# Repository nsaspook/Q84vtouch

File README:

Turbopump RS485 DCU readout emulator

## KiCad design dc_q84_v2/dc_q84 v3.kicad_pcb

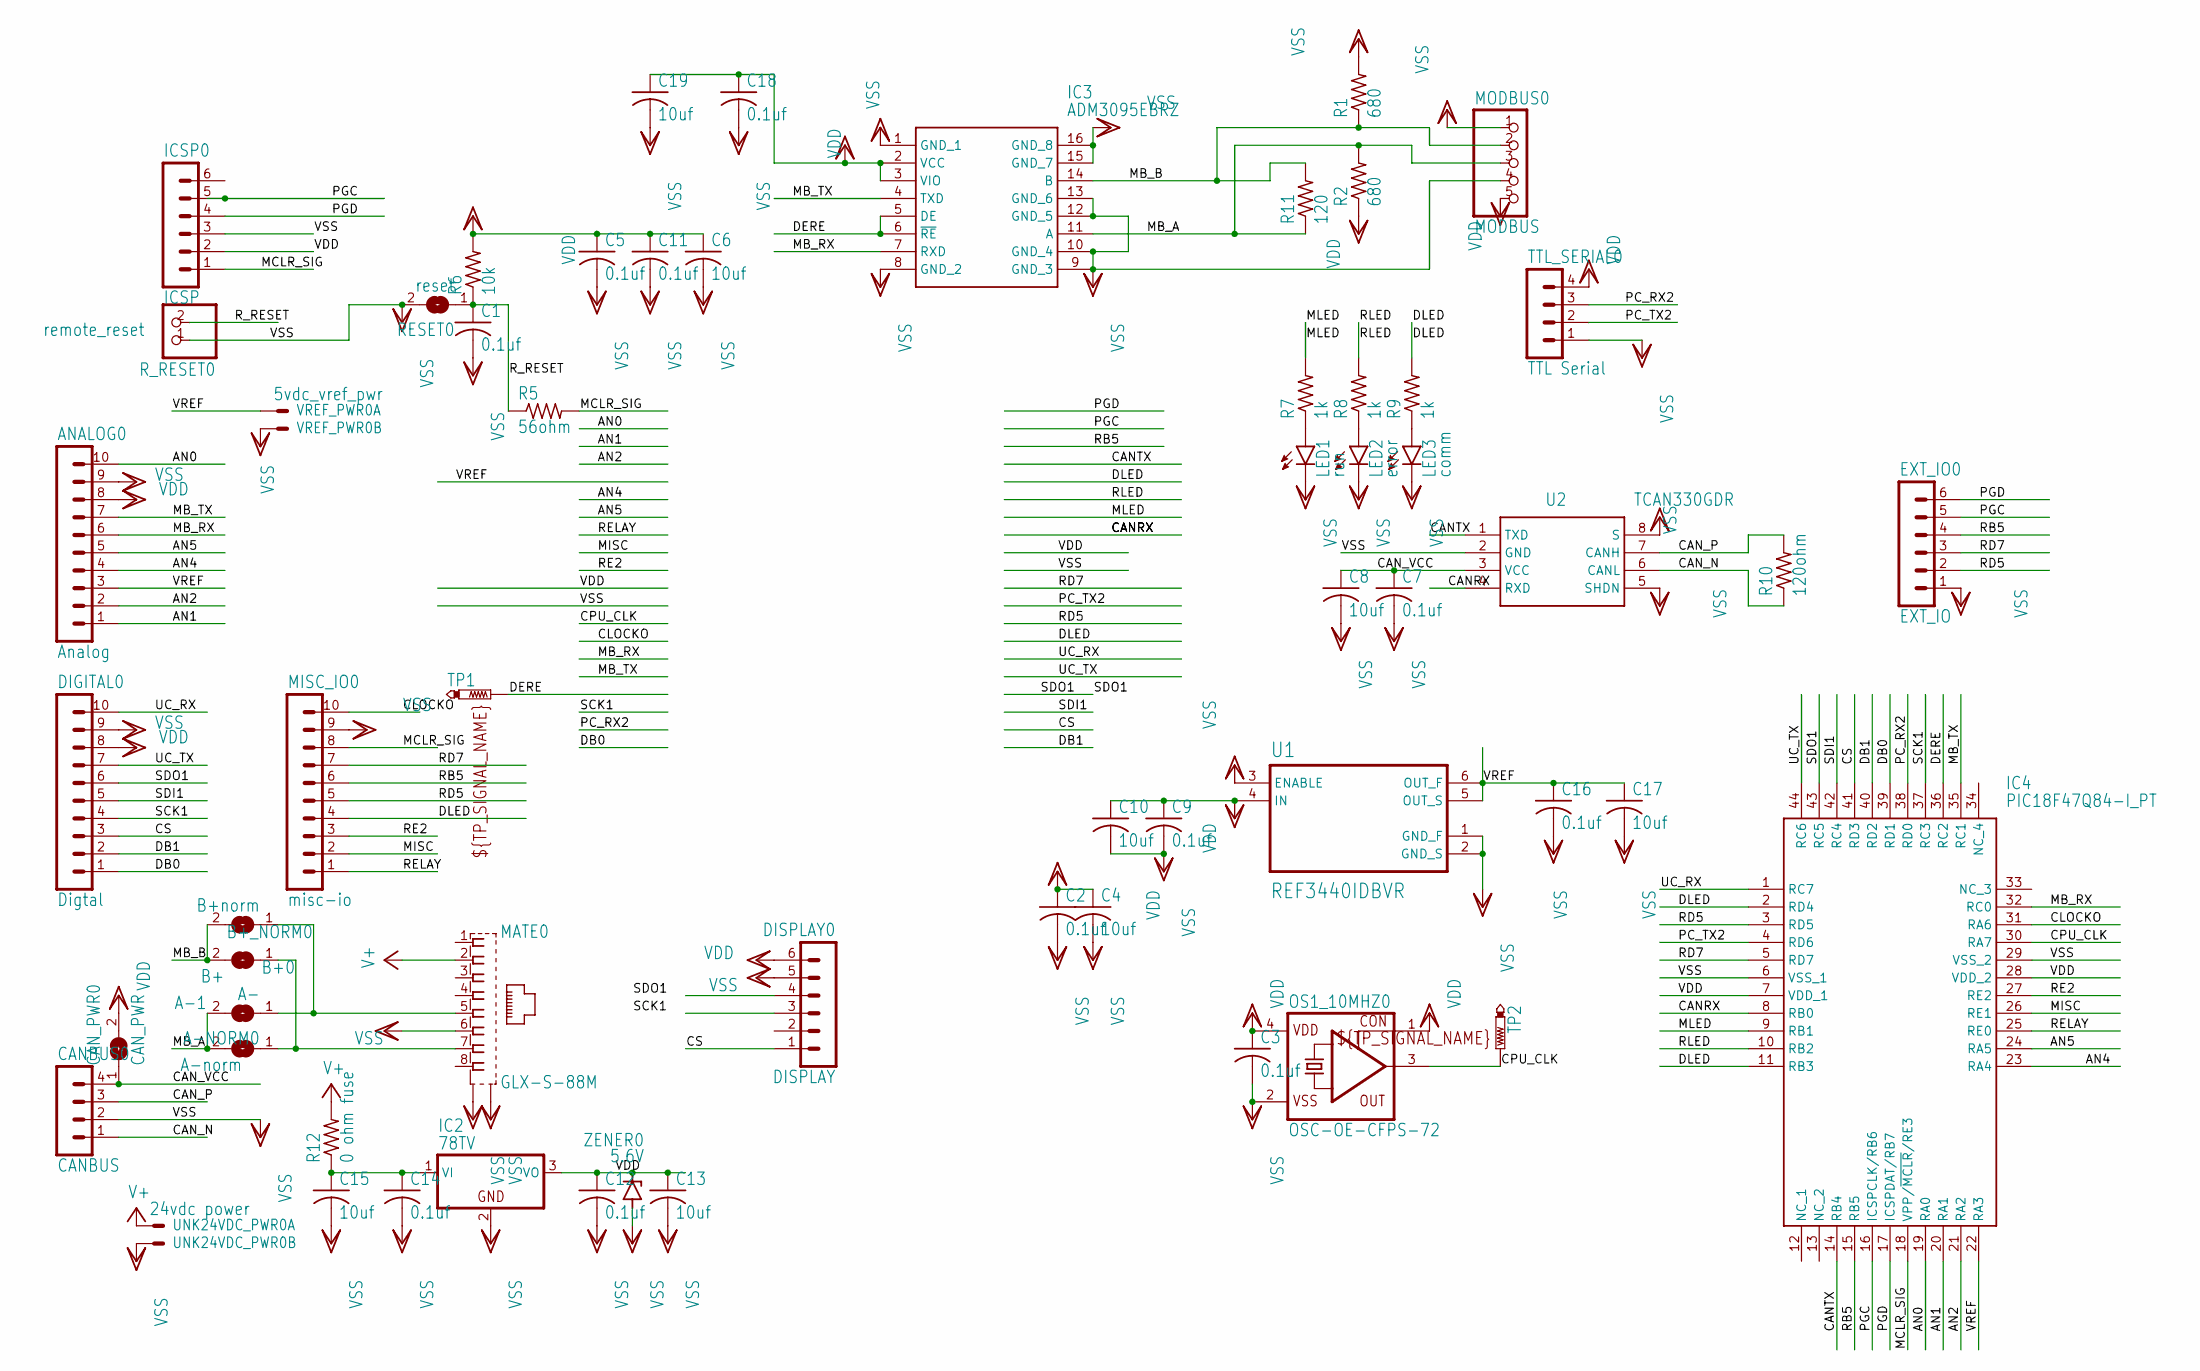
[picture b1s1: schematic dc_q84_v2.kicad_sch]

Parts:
A-1: A-; SJ
A-NORM0: A-norm; SJ
ANALOG0: Analog; MA10-1
B+0: B+; SJ
B+_NORM0: B+norm; SJ
C1, C2, C3, C5, C7, C9, C11, C12, C14, C16, C18: 0.1uf; C0805
C4, C6, C8, C10, C13, C15, C17, C19: 10uf; C0805
CANBUS0: CANBUS; MA04-1
CAN_PWR0: CAN_PWR; SJ
DIGITAL0: Digtal; MA10-1
DISPLAY0: DISPLAY; MA06-1
EXT_IO0: EXT_IO; MA06-1
IC2: 78TV; TO220V
IC3: ADM3095EBRZ; SOIC127P600X175-16N
IC4: PIC18F47Q84-I_PT; QFP80P1200X1200X120-44N
ICSP0: ICSP; MA06-1
LED1: run; CHIPLED_0805
LED2: error; CHIPLED_0805
LED3: comm; CHIPLED_0805
MATE0: GLX-S-88M
MISC_IO0: misc-io; MA10-1
MODBUS0: MODBUS; 1X05
OS1_10MHZ0: OSC-OE-CFPS-72; 7.2X5.2-4-PAD
R1, R2: 680; R0805
R5: 56ohm; R0805
R6: 10k; R0805
R7, R8, R9: 1k; R0805
R10: 120ohm; R0805
R11: 120; R0805
R12: 0 ohm fuse; R1206
RESET0: reset; SJ
R_RESET0: remote_reset; 1X02
TP1, TP2: PTR1PAD1-13; P1-13
TTL_SERIAL0: TTL Serial; MA04-1
U1: REF3440IDBVR; SOT95P280X145-6N
U2: TCAN330GDR; SOIC127P600X175-8N
UNK24VDC_PWR0: 24vdc power; 22-23-2021
VREF_PWR0: 5vdc_vref_pwr; 22-23-2021
ZENER0: 5.6V; SMB

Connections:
AN0: ANALOG0.10, IC4.19 (RA0)
AN1: ANALOG0.1, IC4.20 (RA1)
AN2: ANALOG0.2, IC4.21 (RA2)
AN4: ANALOG0.4, IC4.23 (RA4)
AN5: ANALOG0.5, IC4.24 (RA5)
CANRX: IC4.8 (RB0), U2.4 (RXD)
CANTX: IC4.14 (RB4), U2.1 (TXD)
CAN_N: CANBUS0.1, R10.1, U2.6 (CANL)
CAN_P: CANBUS0.3, R10.2, U2.7 (CANH)
CAN_VCC: C7.1, C8.1, CANBUS0.4, CAN_PWR0.1, U2.3 (VCC)
CLOCKO: IC4.31 (RA6), MISC_IO0.10
CPU_CLK: IC4.30 (RA7), OS1_10MHZ0.3 (OUT), TP2.TP
CS: DIGITAL0.3, DISPLAY0.1, IC4.41 (RD3)
DB0: DIGITAL0.1, IC4.39 (RD1)
DB1: DIGITAL0.2, IC4.40 (RD2)
DERE: IC3.5 (DE), IC3.6 (~RE), IC4.36 (RC2), TP1.TP
DLED: IC4.2 (RD4), IC4.11 (RB3), MISC_IO0.4, R9.2
MB_A: A-1.2, A-NORM0.2, IC3.11 (A), MODBUS0.3, R2.2, R11.1
MB_B: B+0.2, B+_NORM0.2, IC3.14 (B), MODBUS0.2, R1.1, R11.2
MB_RX: ANALOG0.6, IC3.7 (RXD), IC4.32 (RC0)
MB_TX: ANALOG0.7, IC3.4 (TXD), IC4.35 (RC1)
MCLR_SIG: IC4.18 (VPP/~MCLR/RE3), ICSP0.1, MISC_IO0.8, R5.2
MISC: IC4.26 (RE1), MISC_IO0.2
MLED: IC4.9 (RB1), R7.2
unnamed: A-NORM0.1, B+0.1, MATE0.7
unnamed: C14.1, C15.1, IC2.1 (VI), R12.1
unnamed: A-1.1, B+_NORM0.1, MATE0.5
unnamed: LED1.A, R7.1
unnamed: LED2.A, R8.1
unnamed: LED3.A, R9.1
PC_RX2: IC4.38 (RD0), TTL_SERIAL0.3
PC_TX2: IC4.4 (RD6), TTL_SERIAL0.2
PGC: EXT_IO0.5, IC4.16 (ICSPCLK/RB6), ICSP0.5
PGD: EXT_IO0.6, IC4.17 (ICSPDAT/RB7), ICSP0.4
RB5: EXT_IO0.4, IC4.15 (RB5), MISC_IO0.6
RD5: EXT_IO0.2, IC4.3 (RD5), MISC_IO0.5
RD7: EXT_IO0.3, IC4.5 (RD7), MISC_IO0.7
RE2: IC4.27 (RE2), MISC_IO0.3
RELAY: IC4.25 (RE0), MISC_IO0.1
RLED: IC4.10 (RB2), R8.2
R_RESET: C1.1, R5.1, R6.1, RESET0.1, R_RESET0.2
SCK1: DIGITAL0.4, DISPLAY0.3, IC4.37 (RC3)
SDI1: DIGITAL0.5, IC4.42 (RC4)
SDO1: DIGITAL0.6, DISPLAY0.4, IC4.43 (RC5)
UC_RX: DIGITAL0.10, IC4.1 (RC7)
UC_TX: DIGITAL0.7, IC4.44 (RC6)
V+: MATE0.2, R12.2, UNK24VDC_PWR0.1
VDD: ANALOG0.8, C2.1, C3.1, C4.1, C5.1, C6.1, C9.1, C10.1, C11.1, C12.1, C13.1, C18.1, C19.1, CAN_PWR0.2, DIGITAL0.8, DISPLAY0.6, IC2.3 (VO), IC3.2 (VCC), IC3.3 (VIO), IC4.7 (VDD_1), IC4.28 (VDD_2), ICSP0.2, MODBUS0.5, OS1_10MHZ0.1 (CON), OS1_10MHZ0.4 (VDD), R2.1, R6.2, TTL_SERIAL0.4, U1.4 (IN), ZENER0.C
VREF: ANALOG0.3, C16.1, C17.1, IC4.22 (RA3), U1.5 (OUT_S), U1.6 (OUT_F), VREF_PWR0.1
VSS: ANALOG0.9, C1.2, C2.2, C3.2, C4.2, C5.2, C6.2, C7.2, C8.2, C9.2, C10.2, C11.2, C12.2, C13.2, C14.2, C15.2, C16.2, C17.2, C18.2, C19.2, CANBUS0.2, DIGITAL0.9, DISPLAY0.5, EXT_IO0.1, IC2.2 (GND), IC3.1 (GND_1), IC3.8 (GND_2), IC3.9 (GND_3), IC3.10 (GND_4), IC3.12 (GND_5), IC3.13 (GND_6), IC3.15 (GND_7), IC3.16 (GND_8), IC4.6 (VSS_1), IC4.29 (VSS_2), ICSP0.3, LED1.C, LED2.C, LED3.C, MATE0.6, MATE0.S1, MATE0.S2, MISC_IO0.9, MODBUS0.1, MODBUS0.4, OS1_10MHZ0.2 (VSS), R1.2, RESET0.2, R_RESET0.1, TTL_SERIAL0.1, U1.1 (GND_F), U1.2 (GND_S), U1.3 (ENABLE), U2.2 (GND), U2.5 (SHDN), U2.8 (S), UNK24VDC_PWR0.2, VREF_PWR0.2, ZENER0.A

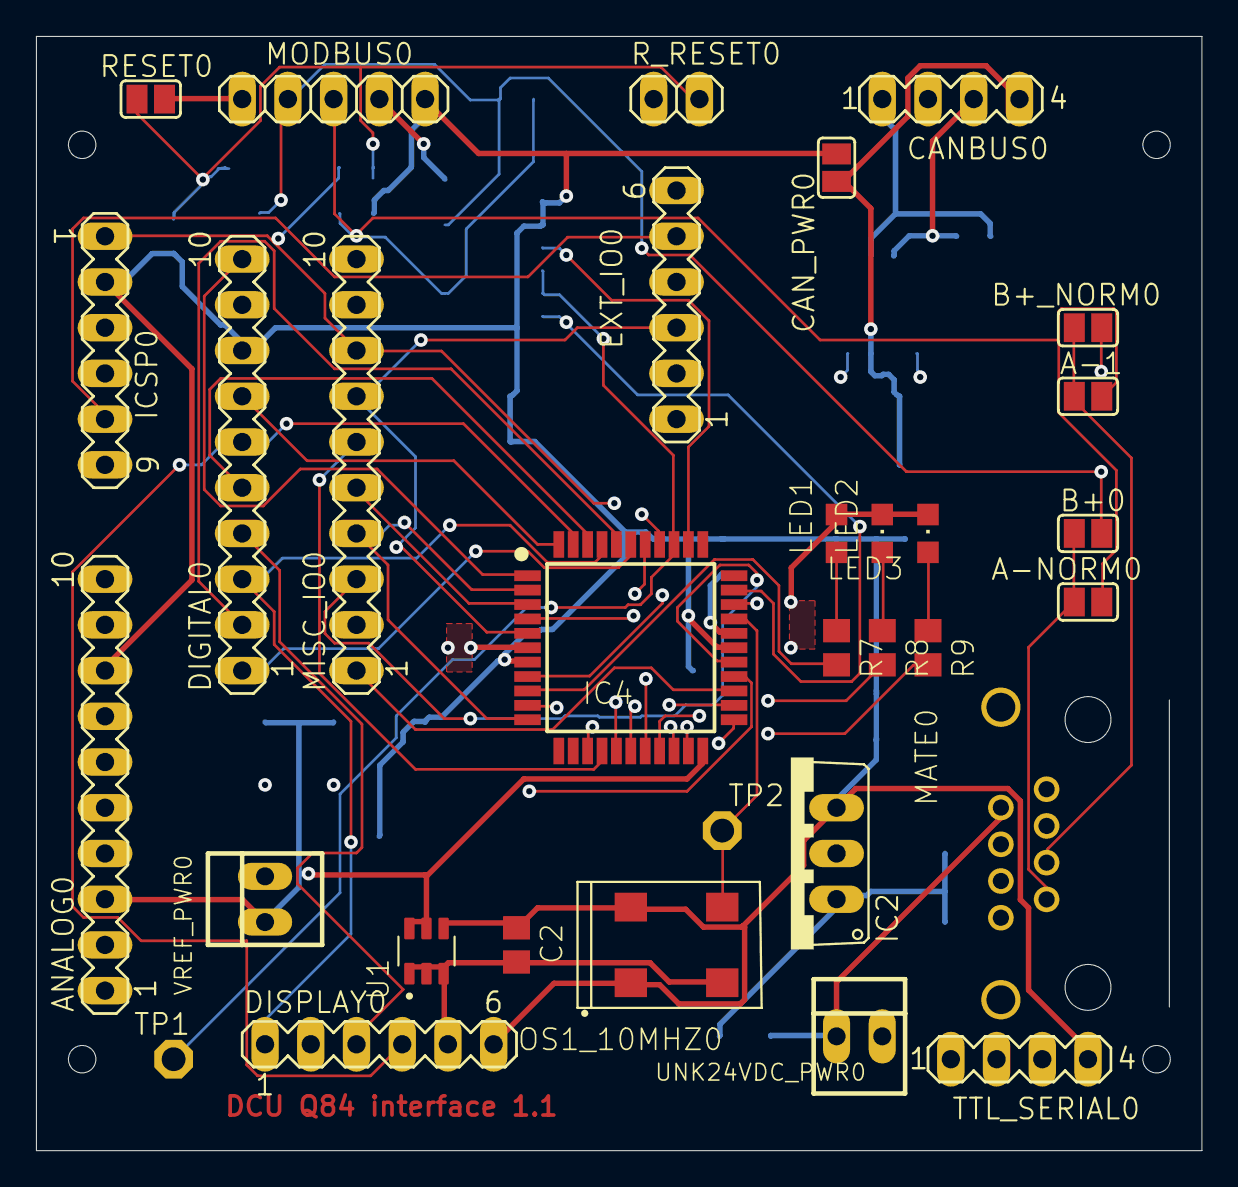
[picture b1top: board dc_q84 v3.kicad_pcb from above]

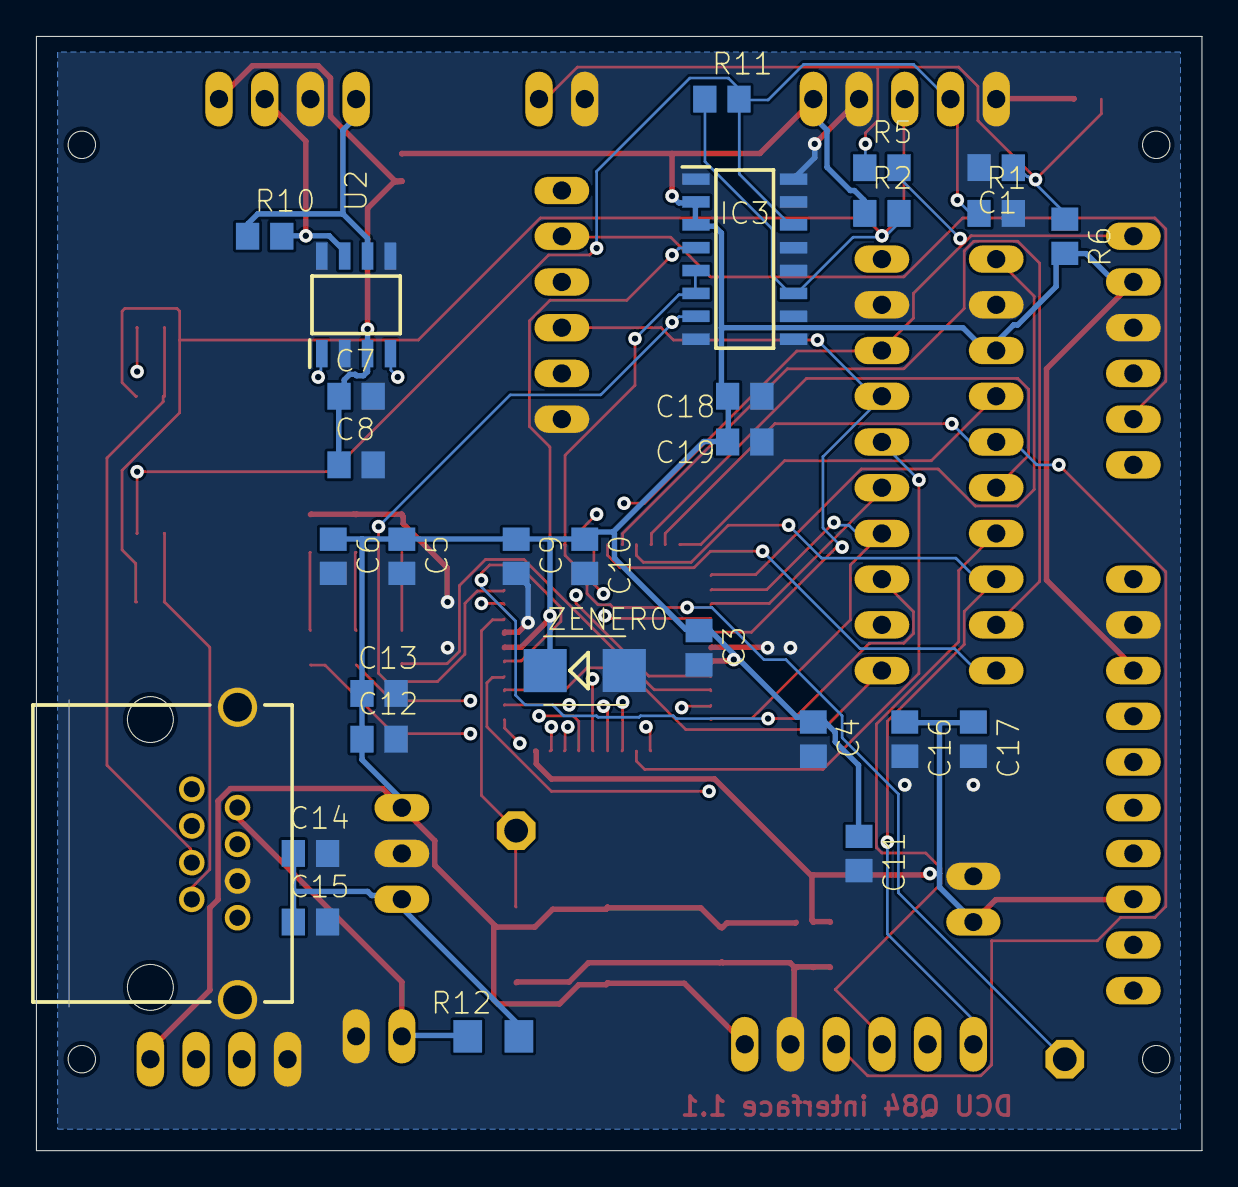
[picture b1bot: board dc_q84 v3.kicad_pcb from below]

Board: 4 copper layers, 64.8 x 61.9 mm, 64 parts (28 on the bottom side), 50 nets.

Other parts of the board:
@HOLE0, @HOLE1, @HOLE2, @HOLE3: (no value)

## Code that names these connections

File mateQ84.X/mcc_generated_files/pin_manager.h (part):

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// get/set channel_ANA0 aliases
#define channel_ANA0_TRIS                 TRISAbits.TRISA0
#define channel_ANA0_LAT                  LATAbits.LATA0
#define channel_ANA0_PORT                 PORTAbits.RA0
#define channel_ANA0_WPU                  WPUAbits.WPUA0
#define channel_ANA0_OD                   ODCONAbits.ODCA0
#define channel_ANA0_ANS                  ANSELAbits.ANSELA0
#define channel_ANA0_SetHigh()            do { LATAbits.LATA0 = 1; } while(0)
#define channel_ANA0_SetLow()             do { LATAbits.LATA0 = 0; } while(0)
#define channel_ANA0_Toggle()             do { LATAbits.LATA0 = ~LATAbits.LATA0; } while(0)
#define channel_ANA0_GetValue()           PORTAbits.RA0
#define channel_ANA0_SetDigitalInput()    do { TRISAbits.TRISA0 = 1; } while(0)
#define channel_ANA0_SetDigitalOutput()   do { TRISAbits.TRISA0 = 0; } while(0)
#define channel_ANA0_SetPullup()          do { WPUAbits.WPUA0 = 1; } while(0)
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// get/set M_SWITCH aliases
#define M_SWITCH_TRIS                 TRISAbits.TRISA1
#define M_SWITCH_LAT                  LATAbits.LATA1
#define M_SWITCH_PORT                 PORTAbits.RA1
#define M_SWITCH_WPU                  WPUAbits.WPUA1
#define M_SWITCH_OD                   ODCONAbits.ODCA1
#define M_SWITCH_ANS                  ANSELAbits.ANSELA1
#define M_SWITCH_SetHigh()            do { LATAbits.LATA1 = 1; } while(0)
#define M_SWITCH_SetLow()             do { LATAbits.LATA1 = 0; } while(0)
#define M_SWITCH_Toggle()             do { LATAbits.LATA1 = ~LATAbits.LATA1; } while(0)
#define M_SWITCH_GetValue()           PORTAbits.RA1
#define M_SWITCH_SetDigitalInput()    do { TRISAbits.TRISA1 = 1; } while(0)
#define M_SWITCH_SetDigitalOutput()   do { TRISAbits.TRISA1 = 0; } while(0)
#define M_SWITCH_SetPullup()          do { WPUAbits.WPUA1 = 1; } while(0)
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// get/set L_SWITCH aliases
#define L_SWITCH_TRIS                 TRISAbits.TRISA2
#define L_SWITCH_LAT                  LATAbits.LATA2
#define L_SWITCH_PORT                 PORTAbits.RA2
#define L_SWITCH_WPU                  WPUAbits.WPUA2
#define L_SWITCH_OD                   ODCONAbits.ODCA2
#define L_SWITCH_ANS                  ANSELAbits.ANSELA2
#define L_SWITCH_SetHigh()            do { LATAbits.LATA2 = 1; } while(0)
#define L_SWITCH_SetLow()             do { LATAbits.LATA2 = 0; } while(0)
#define L_SWITCH_Toggle()             do { LATAbits.LATA2 = ~LATAbits.LATA2; } while(0)
#define L_SWITCH_GetValue()           PORTAbits.RA2
#define L_SWITCH_SetDigitalInput()    do { TRISAbits.TRISA2 = 1; } while(0)
#define L_SWITCH_SetDigitalOutput()   do { TRISAbits.TRISA2 = 0; } while(0)
#define L_SWITCH_SetPullup()          do { WPUAbits.WPUA2 = 1; } while(0)
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#define RA3_SetHigh()            do { LATAbits.LATA3 = 1; } while(0)
#define RA3_SetLow()             do { LATAbits.LATA3 = 0; } while(0)
#define RA3_Toggle()             do { LATAbits.LATA3 = ~LATAbits.LATA3; } while(0)
#define RA3_GetValue()              PORTAbits.RA3
#define RA3_SetDigitalInput()    do { TRISAbits.TRISA3 = 1; } while(0)
#define RA3_SetDigitalOutput()   do { TRISAbits.TRISA3 = 0; } while(0)
#define RA3_SetPullup()             do { WPUAbits.WPUA3 = 1; } while(0)
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// get/set channel_ANA4 aliases
#define channel_ANA4_TRIS                 TRISAbits.TRISA4
#define channel_ANA4_LAT                  LATAbits.LATA4
#define channel_ANA4_PORT                 PORTAbits.RA4
#define channel_ANA4_WPU                  WPUAbits.WPUA4
#define channel_ANA4_OD                   ODCONAbits.ODCA4
#define channel_ANA4_ANS                  ANSELAbits.ANSELA4
#define channel_ANA4_SetHigh()            do { LATAbits.LATA4 = 1; } while(0)
#define channel_ANA4_SetLow()             do { LATAbits.LATA4 = 0; } while(0)
#define channel_ANA4_Toggle()             do { LATAbits.LATA4 = ~LATAbits.LATA4; } while(0)
#define channel_ANA4_GetValue()           PORTAbits.RA4
#define channel_ANA4_SetDigitalInput()    do { TRISAbits.TRISA4 = 1; } while(0)
#define channel_ANA4_SetDigitalOutput()   do { TRISAbits.TRISA4 = 0; } while(0)
#define channel_ANA4_SetPullup()          do { WPUAbits.WPUA4 = 1; } while(0)
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// get/set A_SWITCH aliases
#define A_SWITCH_TRIS                 TRISAbits.TRISA5
#define A_SWITCH_LAT                  LATAbits.LATA5
#define A_SWITCH_PORT                 PORTAbits.RA5
#define A_SWITCH_WPU                  WPUAbits.WPUA5
#define A_SWITCH_OD                   ODCONAbits.ODCA5
#define A_SWITCH_ANS                  ANSELAbits.ANSELA5
#define A_SWITCH_SetHigh()            do { LATAbits.LATA5 = 1; } while(0)
#define A_SWITCH_SetLow()             do { LATAbits.LATA5 = 0; } while(0)
#define A_SWITCH_Toggle()             do { LATAbits.LATA5 = ~LATAbits.LATA5; } while(0)
#define A_SWITCH_GetValue()           PORTAbits.RA5
#define A_SWITCH_SetDigitalInput()    do { TRISAbits.TRISA5 = 1; } while(0)
#define A_SWITCH_SetDigitalOutput()   do { TRISAbits.TRISA5 = 0; } while(0)
#define A_SWITCH_SetPullup()          do { WPUAbits.WPUA5 = 1; } while(0)
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#define RB0_SetHigh()            do { LATBbits.LATB0 = 1; } while(0)
#define RB0_SetLow()             do { LATBbits.LATB0 = 0; } while(0)
#define RB0_Toggle()             do { LATBbits.LATB0 = ~LATBbits.LATB0; } while(0)
#define RB0_GetValue()              PORTBbits.RB0
#define RB0_SetDigitalInput()    do { TRISBbits.TRISB0 = 1; } while(0)
#define RB0_SetDigitalOutput()   do { TRISBbits.TRISB0 = 0; } while(0)
#define RB0_SetPullup()             do { WPUBbits.WPUB0 = 1; } while(0)
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// get/set MLED aliases
#define MLED_TRIS                 TRISBbits.TRISB1
#define MLED_LAT                  LATBbits.LATB1
#define MLED_PORT                 PORTBbits.RB1
#define MLED_WPU                  WPUBbits.WPUB1
#define MLED_OD                   ODCONBbits.ODCB1
#define MLED_ANS                  ANSELBbits.ANSELB1
#define MLED_SetHigh()            do { LATBbits.LATB1 = 1; } while(0)
#define MLED_SetLow()             do { LATBbits.LATB1 = 0; } while(0)
#define MLED_Toggle()             do { LATBbits.LATB1 = ~LATBbits.LATB1; } while(0)
#define MLED_GetValue()           PORTBbits.RB1
#define MLED_SetDigitalInput()    do { TRISBbits.TRISB1 = 1; } while(0)
#define MLED_SetDigitalOutput()   do { TRISBbits.TRISB1 = 0; } while(0)
#define MLED_SetPullup()          do { WPUBbits.WPUB1 = 1; } while(0)
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// get/set RLED aliases
#define RLED_TRIS                 TRISBbits.TRISB2
#define RLED_LAT                  LATBbits.LATB2
#define RLED_PORT                 PORTBbits.RB2
#define RLED_WPU                  WPUBbits.WPUB2
#define RLED_OD                   ODCONBbits.ODCB2
#define RLED_ANS                  ANSELBbits.ANSELB2
#define RLED_SetHigh()            do { LATBbits.LATB2 = 1; } while(0)
#define RLED_SetLow()             do { LATBbits.LATB2 = 0; } while(0)
#define RLED_Toggle()             do { LATBbits.LATB2 = ~LATBbits.LATB2; } while(0)
#define RLED_GetValue()           PORTBbits.RB2
#define RLED_SetDigitalInput()    do { TRISBbits.TRISB2 = 1; } while(0)
#define RLED_SetDigitalOutput()   do { TRISBbits.TRISB2 = 0; } while(0)
#define RLED_SetPullup()          do { WPUBbits.WPUB2 = 1; } while(0)
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// get/set DLED1 aliases
#define DLED1_TRIS                 TRISBbits.TRISB3
#define DLED1_LAT                  LATBbits.LATB3
#define DLED1_PORT                 PORTBbits.RB3
#define DLED1_WPU                  WPUBbits.WPUB3
#define DLED1_OD                   ODCONBbits.ODCB3
#define DLED1_ANS                  ANSELBbits.ANSELB3
#define DLED1_SetHigh()            do { LATBbits.LATB3 = 1; } while(0)
#define DLED1_SetLow()             do { LATBbits.LATB3 = 0; } while(0)
#define DLED1_Toggle()             do { LATBbits.LATB3 = ~LATBbits.LATB3; } while(0)
#define DLED1_GetValue()           PORTBbits.RB3
#define DLED1_SetDigitalInput()    do { TRISBbits.TRISB3 = 1; } while(0)
#define DLED1_SetDigitalOutput()   do { TRISBbits.TRISB3 = 0; } while(0)
#define DLED1_SetPullup()          do { WPUBbits.WPUB3 = 1; } while(0)
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#define RB4_SetHigh()            do { LATBbits.LATB4 = 1; } while(0)
#define RB4_SetLow()             do { LATBbits.LATB4 = 0; } while(0)
#define RB4_Toggle()             do { LATBbits.LATB4 = ~LATBbits.LATB4; } while(0)
#define RB4_GetValue()              PORTBbits.RB4
#define RB4_SetDigitalInput()    do { TRISBbits.TRISB4 = 1; } while(0)
#define RB4_SetDigitalOutput()   do { TRISBbits.TRISB4 = 0; } while(0)
#define RB4_SetPullup()             do { WPUBbits.WPUB4 = 1; } while(0)
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// get/set IO_RB5 aliases
#define IO_RB5_TRIS                 TRISBbits.TRISB5
#define IO_RB5_LAT                  LATBbits.LATB5
#define IO_RB5_PORT                 PORTBbits.RB5
#define IO_RB5_WPU                  WPUBbits.WPUB5
#define IO_RB5_OD                   ODCONBbits.ODCB5
#define IO_RB5_ANS                  ANSELBbits.ANSELB5
#define IO_RB5_SetHigh()            do { LATBbits.LATB5 = 1; } while(0)
#define IO_RB5_SetLow()             do { LATBbits.LATB5 = 0; } while(0)
#define IO_RB5_Toggle()             do { LATBbits.LATB5 = ~LATBbits.LATB5; } while(0)
#define IO_RB5_GetValue()           PORTBbits.RB5
#define IO_RB5_SetDigitalInput()    do { TRISBbits.TRISB5 = 1; } while(0)
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
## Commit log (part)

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2023-06-20 up up#
2023-09-27 :wq up
2023-11-11 change can filter method to maybe allow for node ID from the CPU ID
2023-12-22 version 1.0 production release
2024-01-01 iup[
2024-02-02 Three canbus packet logging updates
2024-06-10 dimming updates to master
2024-06-18 float fixes
2024-06-19 convert to syslog for perror
2024-06-27 up:wq
2024-10-12 v2.01
2024-11-17 up:wq `:wq
2024-12-03 case files
2024-12-16 new rj45
2024-12-16 1.3 board
2024-12-31 change pcb name
2025-01-30 up V2.03
2025-02-16 rename to ha_canfd
2025-05-22 minor FM comm fixes and lib updates
2025-08-09 change ipaddress
2025-08-17 up docs up# new file: html/adc_8c.html
2025-09-02 up restart fixes
2025-09-04 up restart code

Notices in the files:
mateQ84.X/mcc_generated_files/pin_manager.h:
(c) 2018 Microchip Technology Inc. and its subsidiaries.
